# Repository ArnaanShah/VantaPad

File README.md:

# VantaPad 👽

A Hackpad made as a part of [Hackclub's Blueprint](https://blueprint.hackclub.com/home) program. VantaPad is a sleek black macropad I will use for controlling simple functions on my computer that I currently do by hand. It is one of my first hardware projects and I built it so I could learn many valuable skills such as schematic design, PCB design, Firmware programming, and more.

## How to use
**Brief intro on how to get up and running with VantaPad**

1. Order all the parts based off the BOM
2. Solder your electrical components onto your PCB based on the models and schematics
3. Assemble your case using the hardware provided
4. Plug your microcontroller into your computer and flash your firmware
5. You're done! Read the rest of this doc to understand what it can do.

## Features 
**What I included on my build.**

- Black Case - A case in the shape of a hexagon with the logo embossed near the bottom.
- 6 Keys in 3x2 layout - Top row is used for resetting screen, taking screenshots, and play/pause. Bottom row has macros for reopening tabs, auto clicking, and cycling layers.  
- 3 RGB LEDs - Lights up a constant looping effect that fades in and out through the case. 
- Rotary Encoder - Layer 1 is Volume, Layer 2 is Tab Scrolling, Layer 3 is undo/redo
- 128x32 OLED Display - Shows important info like what layer you're on and auto clicker status. Also, shows idle animations and reactions when you press a key.
  
## PCB 
**The design around my PCB. This Includes the schematic I made, the PCB, and more.** 

I designed my PCB in KiCad 9.0! It was fun to use this app because it was pretty beginner friendly and intuitive. It also had some extra built in features so I didn't have to download another app.

Schematic: 

PCB:

3d VIEW:

I used KiCad's built-in Image Converter to make a footprint of my logo:

## CAD
**The CAD model I made.**

I modeled this project in Fusion 360 because I've used it before. My plan is that I can assemble the whole thing with 6 screws. 4 on the actual case and 2 connecting the PCB and PCB plate to the case. I added a 10 degree tilt to make it easier to see. There are 3 separate 3d printed parts; the top, the plate, and the bottom. The top has the VantaPad logo on it because it looks lit. 😎

Pictures 📸:

## Firmware 
**Insight into the Firmware**

I wrote all the firmware in QMK. I spent a long time fixing problems when writing the code. These problems were things like the firmware not compiling, not knowing how to use all my extra features, and more. The QMK docs can be confusing but I found many resources online to help me. 

- The 6 keys are mapped as shown but can be easily changed
```
║ Screen Reset ║ Screenshot   ║ Play/Pause  ║

║ Reopen Tab   ║ Auto Clicker ║ Layer Cycle ║
```
```// ---------- Keymaps ----------
const uint16_t PROGMEM keymaps[][MATRIX_ROWS][MATRIX_COLS] = {
    [_BASE] = LAYOUT(
        RESET_SCREEN, SCREENSHOT, KC_MPLY, KC_MUTE, // Top row + Encoder Button
        REOPEN_TAB, AUTO_CLICKER, KC_CYCLE_LAYERS
    ),
};
```
- The rotary encoder controls volume on the first layer, scrolls through browser tabs on the second layer, and undos/redos on the third layer.
  - When you press down on the encoder it always mutes the volume
```
const uint16_t PROGMEM encoder_map[][1][2] = {
    [_BASE]   = { ENCODER_CCW_CW(KC_VOLD, KC_VOLU) },
    [_LAYER1] = { ENCODER_CCW_CW(LCTL(KC_PGUP), LCTL(KC_PGDN)) },
    [_LAYER2] = { ENCODER_CCW_CW(LCTL(KC_Z), LCTL(KC_Y)) },
};
```
- The OLED has 2 animations. Animation 1 is the constant looping animation where my alien is "breathing" with occasional blinks. Animation 2 starts when any key is pressed and it basically makes the alien look surprised and have a lightning bolt above his head. 

- The OLED also has some info on the left of the animation. This includes what layer it is currently using, whether the auto clicker is on, the label "Vantapad", and also my name. 
```
oled_set_cursor(0, 0);
    oled_write_P(PSTR("Arnaan Shah"), false);

    oled_set_cursor(0, 1);
    oled_write_P(PSTR("Vantapad"), false);

    oled_set_cursor(0, 2);
    switch (get_highest_layer(layer_state)) {
        case _BASE:   oled_write_P(PSTR("Layer 1"), false); break;
        case _LAYER1: oled_write_P(PSTR("Layer 2"), false); break;
        case _LAYER2: oled_write_P(PSTR("Layer 3"), false); break;
    }

    oled_set_cursor(0, 3);
    if (auto_clicker_active) {
        oled_write_P(PSTR("AutoClick:ON "), false);
    } else {
        oled_write_P(PSTR("AutoClick:OFF"), false);
    }
```

- The RGB LEDS are set to display red and cycle a constant breathing animation
```
void keyboard_post_init_user(void) {
    rgblight_enable_noeeprom();
    rgblight_sethsv_noeeprom(0, 255, 100);
    rgblight_mode_noeeprom(RGBLIGHT_MODE_BREATHING + 1); 
}
```
## BOM
**What to buy to build this macropad. Does not include all the tools required to build it.**

| Name | Amount | Link |
|---|---|---|
| Cherry MX Switches | 6 | [Adafruit](https://www.adafruit.com/product/4952)|
| DSA Keycaps | 6 | [Adafruit](https://www.adafruit.com/product/4997?srsltid=AfmBOopDyFMg5RxxF-Evr6nBGQDyHVTH-dyfbuGdqPaHn7PWQv5c8-_Q) |
| M3 16mm SHCS Bolts | 5 | [Accu Components](https://accu-components.com/us/metric-cap-head-screws/3822-SSCF-M3-16-A2?srsltid=AfmBOopF9mJr7xpYuq4pjtawdEtUoNOIrShH98uHL0dEVVrOUcjwKY9b) |
| M3 12mm SHCS Bolt | 1 | [Accu Components](https://accu-components.com/us/metric-cap-head-screws/3820-SSCF-M3-12-A2) |
| M3 Hex Nuts | 6 | [Accu Components](https://accu-components.com/us/hexagon-nuts/7888-HPN-M3-A2) |
| In4148 DO-35 Diodes | 7 | [Adafruit](https://www.adafruit.com/product/1641?srsltid=AfmBOoragpyopdxH587co8w9Kl0W3cZMjn9bZIbP4UEYHfyiLFoC3nJv) |
| WS2812B RGB LEDS | 3 | [Adafruit](https://www.adafruit.com/product/4684?srsltid=AfmBOop-1QOhPkmYg3AzDhOUYgR5UXpQo03Vo2tT4txB9Lo8MBpf2Z1e) |
| 0.91" OLED Display | 1 | [Aliexpress](https://www.aliexpress.us/item/3256807215355950.html?src=google&pdp_npi=4%40dis%21USD%211.75%210.87%21%21%21%21%21%40%2112000040595474261%21ppc%21%21%21&src=google&albch=shopping&acnt=708-803-3821&isdl=y&slnk=&plac=&mtctp=&albbt=Google_7_shopping&aff_platform=google&aff_short_key=UneMJZVf&gclsrc=aw.ds&albagn=888888&ds_e_adid=&ds_e_matchtype=&ds_e_device=c&ds_e_network=x&ds_e_product_group_id=&ds_e_product_id=en3256807215355950&ds_e_product_merchant_id=5377576114&ds_e_product_country=US&ds_e_product_language=en&ds_e_product_channel=online&ds_e_product_store_id=&ds_url_v=2&albcp=19558607238&albag=&isSmbAutoCall=false&needSmbHouyi=false&gad_source=1&gad_campaignid=19566915268&gclid=Cj0KCQiAk6rNBhCxARIsAN5mQLsg54LCOzQhSObuPu2m54rcTcgSLZ9bMY2AuwFurhrSghMghQPbqsoaAguWEALw_wcB&gatewayAdapt=glo2usa)|
| EC11 Encoder | 1 | [Adafruit](https://www.adafruit.com/product/377)|
| Seeed Studio XIAO RP2040 | 1 | [Seeed Studio](https://www.seeedstudio.com/XIAO-RP2040-v1-0-p-5026.html) |
| 3d Printed Case | 1 | N/A |

## Extras 🪄
**Miscellaneous related things**

I made the logo design all in Figma and it's based off the "Space Alien" inside Halloween Stickers. 

It's honestly one of my favorite parts of the project because of how cute he is 😅

_

Here are some photos of my brainstorming process. It includes some (really) rough sketches in my notebook and also online. 

_I always start with doing things in my notebook and then move forward from there. It helps me get a very basic idea of what im going to do and how to accomplish it._

_I made this image afterwards just to get a better understanding of how I wanted it to look._

Changes I would still consider making down the line include: 
1. More Information displayed on the OLED - WPM, Time, Date, Volume
2. Adding more animations to the OLED - Spinning alien based on knob, startup screen
3. Making the RGB react - Flash on key press, blink when auto-clicker's active
4. Displaying the PCB through the case somehow

Some resources I used:
- [Joe Scotto's Youtube Channel](https://www.youtube.com/@joe_scotto) (LIFESAVER 🙏)
- [QMK Docs](https://docs.qmk.fm)
- [r/MechanicalKeyboards subreddit](https://www.reddit.com/r/MechanicalKeyboards/) 

# Thanks for reading! If you have any feedback, comments, or questions I would love to hear them and you can always reach out to me!

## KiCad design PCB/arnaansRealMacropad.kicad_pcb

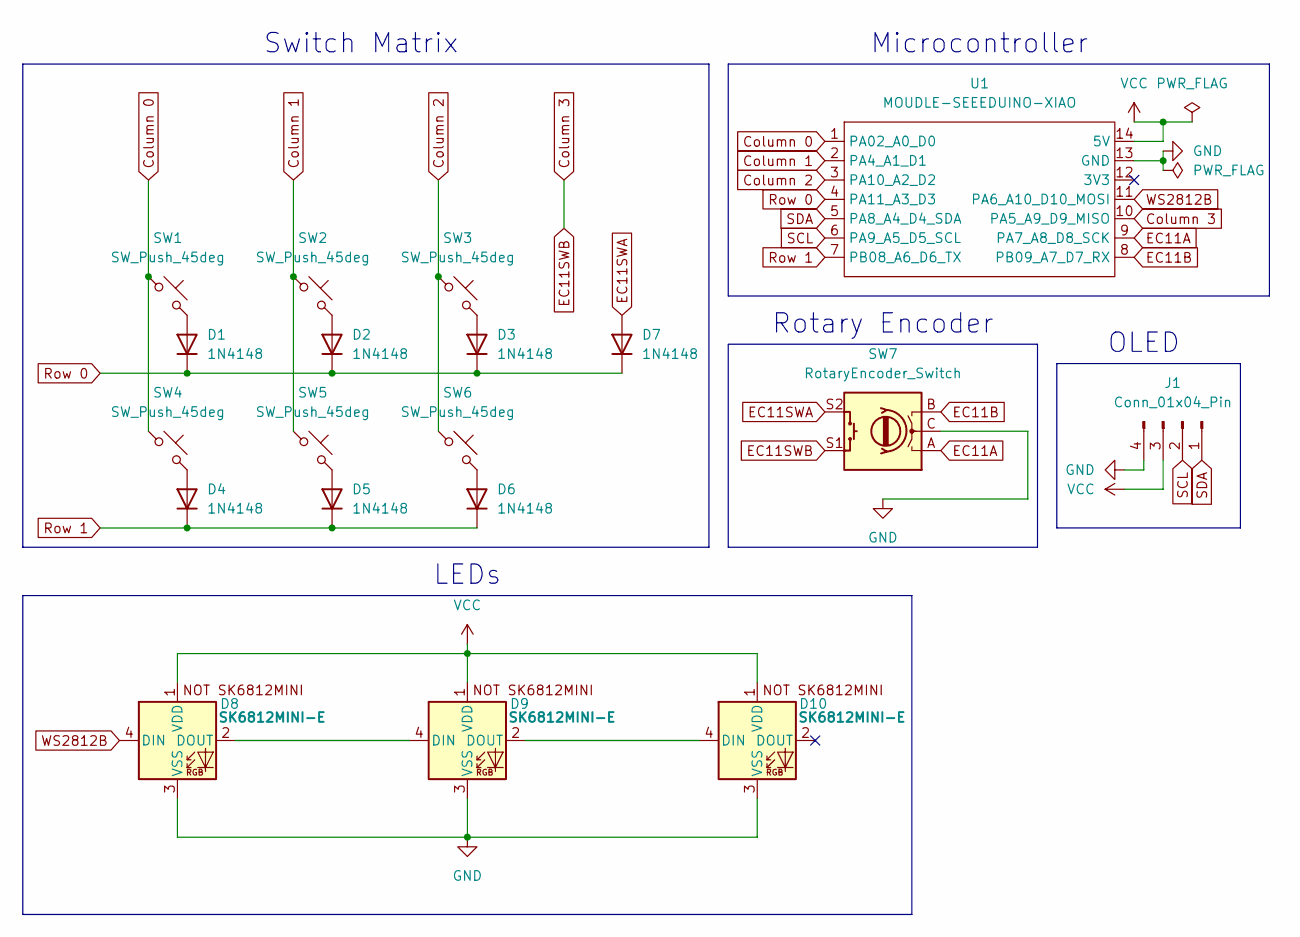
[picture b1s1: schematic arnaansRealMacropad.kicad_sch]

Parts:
D1, D2, D3, D4, D5, D6, D7: 1N4148; D_DO-35_SOD27_P7.62mm_Horizontal
D8, D9, D10: SK6812MINI-E; SK6812MINI-E_fixed
J1: Conn_01x04_Pin; PinHeader_1x04_P2.54mm_Vertical
SW1, SW2, SW3, SW4, SW5, SW6: SW_Push_45deg; SW_Cherry_MX_1.00u_PCB
SW7: RotaryEncoder_Switch; RotaryEncoder_Alps_EC11E-Switch_Vertical_H20mm
U1: MOUDLE-SEEEDUINO-XIAO; XIAO-Generic-Hybrid-14P-2.54-21X17.8MM

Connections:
Column 0: SW1.1, SW4.1, U1.1 (PA02_A0_D0)
Column 1: SW2.1, SW5.1, U1.2 (PA4_A1_D1)
Column 2: SW3.1, SW6.1, U1.3 (PA10_A2_D2)
Column 3: SW7.S1, U1.10 (PA5_A9_D9_MISO)
EC11A: SW7.A, U1.9 (PA7_A8_D8_SCK)
EC11B: SW7.B, U1.8 (PB09_A7_D7_RX)
EC11SWA: D7.2 (A), SW7.S2
GND: D8.3 (VSS), D9.3 (VSS), D10.3 (VSS), J1.4, SW7.C, U1.13 (GND)
unnamed: D1.2 (A), SW1.2
unnamed: D2.2 (A), SW2.2
unnamed: D3.2 (A), SW3.2
unnamed: D4.2 (A), SW4.2
unnamed: D5.2 (A), SW5.2
unnamed: D6.2 (A), SW6.2
unnamed: D8.2 (DOUT), D9.4 (DIN)
unnamed: D9.2 (DOUT), D10.4 (DIN)
Row 0: D1.1 (K), D2.1 (K), D3.1 (K), D7.1 (K), U1.4 (PA11_A3_D3)
Row 1: D4.1 (K), D5.1 (K), D6.1 (K), U1.7 (PB08_A6_D6_TX)
SCL: J1.2, U1.6 (PA9_A5_D5_SCL)
SDA: J1.1, U1.5 (PA8_A4_D4_SDA)
VCC: D8.1 (VDD), D9.1 (VDD), D10.1 (VDD), J1.3, U1.14 (5V)
WS2812B: D8.4 (DIN), U1.11 (PA6_A10_D10_MOSI)

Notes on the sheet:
Rotary Encoder
OLED
Microcontroller
Switch Matrix
LEDs

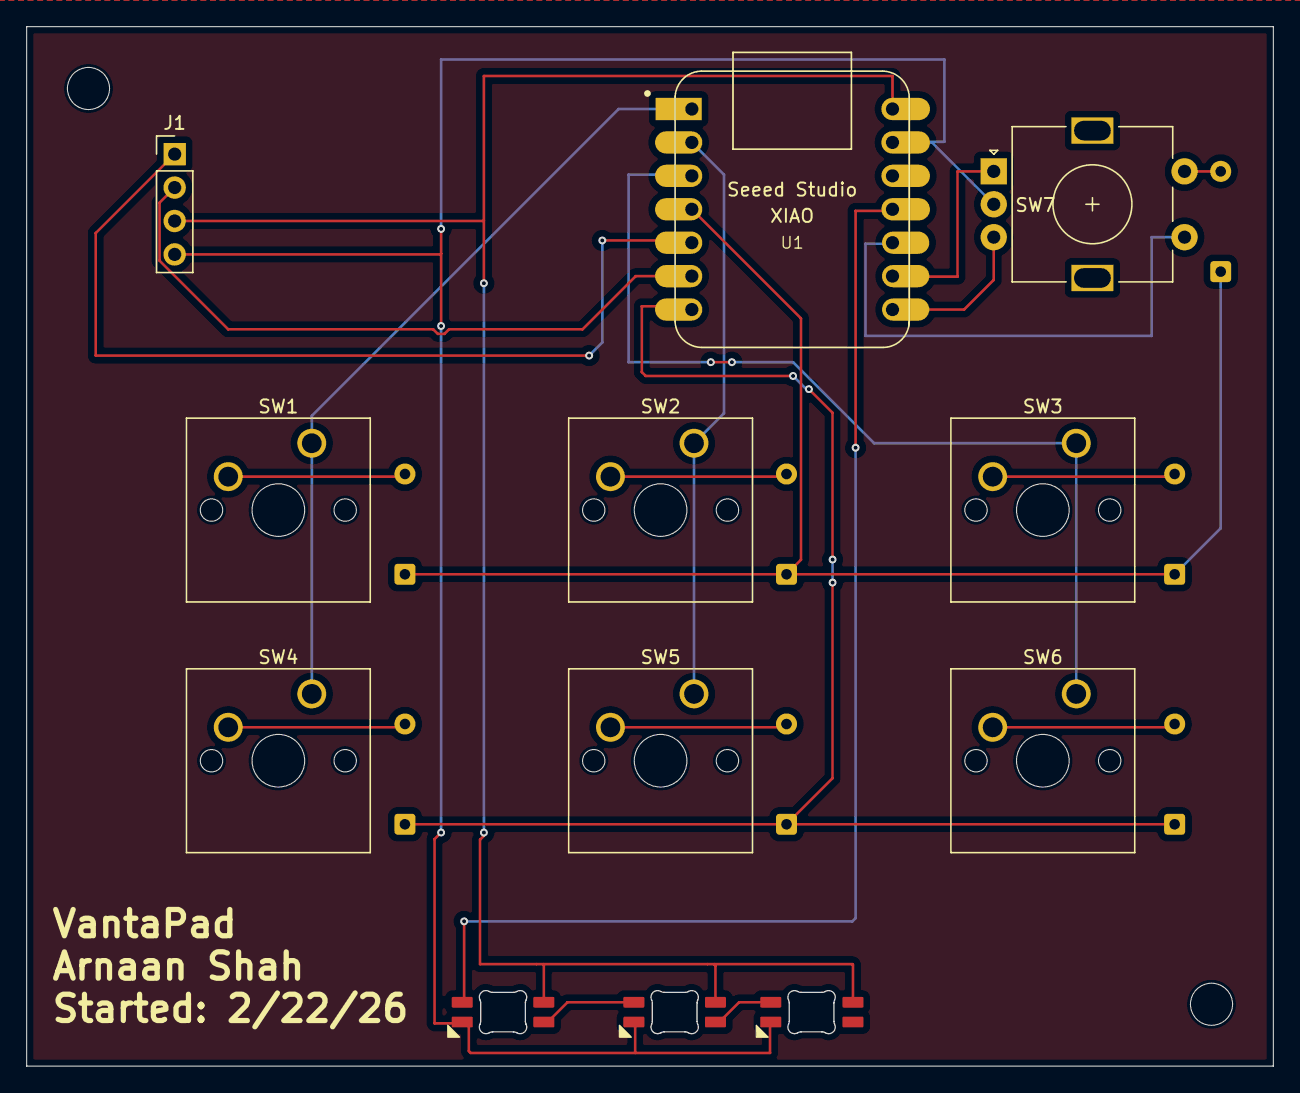
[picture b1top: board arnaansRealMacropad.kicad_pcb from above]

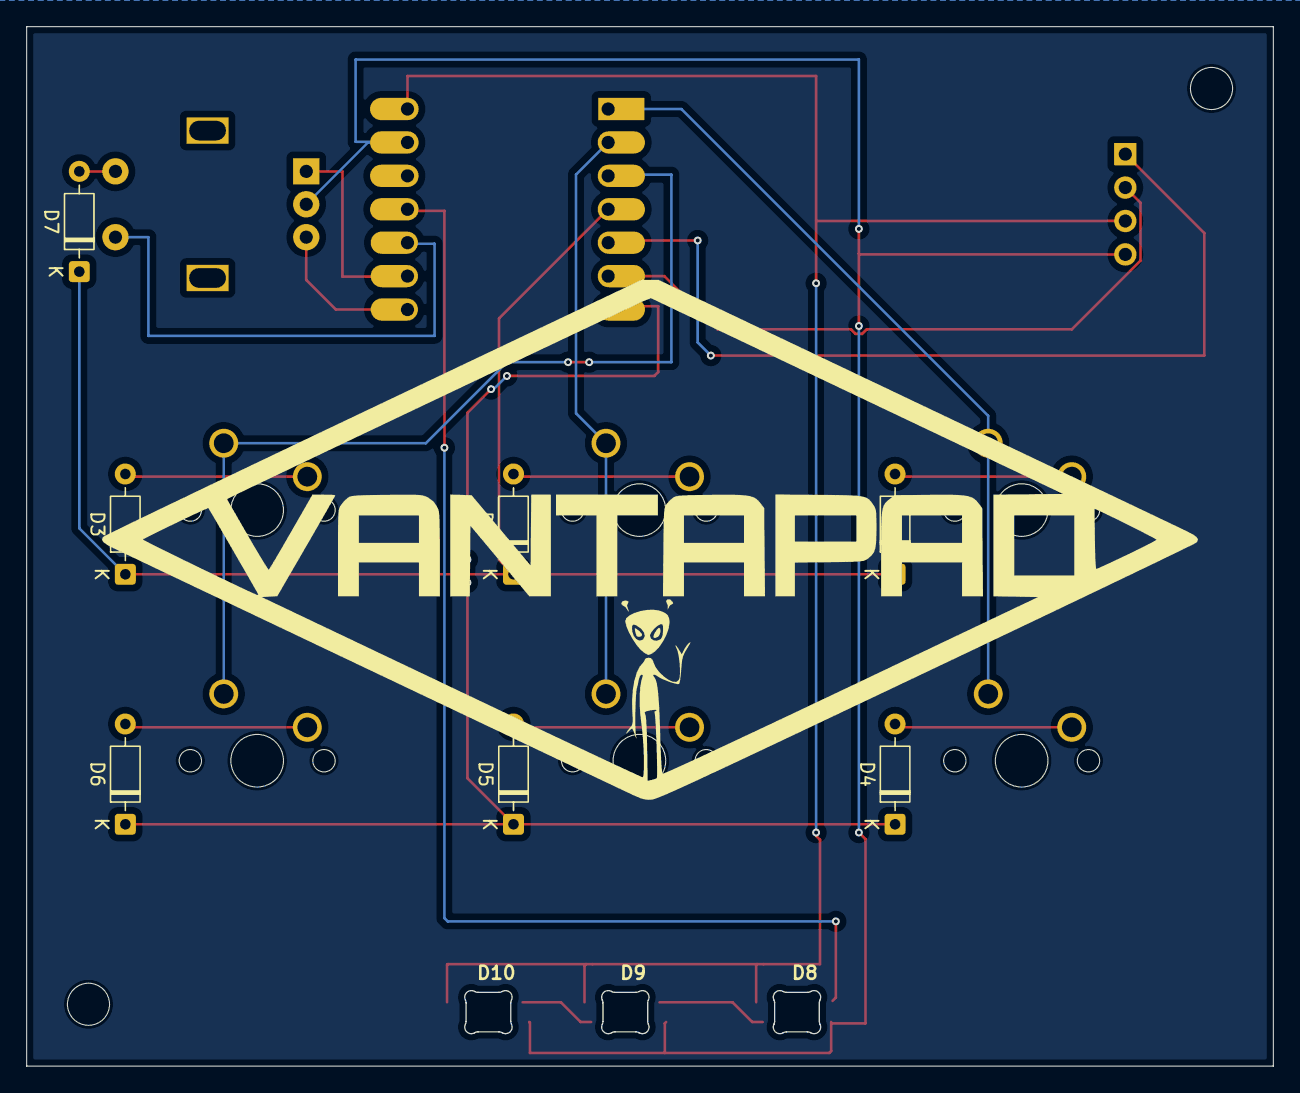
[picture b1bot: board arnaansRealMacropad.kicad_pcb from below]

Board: 2 copper layers, 94.8 x 79.0 mm, 19 parts (10 on the bottom side), 22 nets.

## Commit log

2026-03-06 Added the required files
2026-03-06 Refactor README.md for better structure and clarity
    Updated the README to improve formatting and content clarity.
2026-03-06 Enhance README with images and hyperlinks
    Updated README.md to include images and links.
2026-03-07 Add BOM.csv with components and links
2026-03-07 Enhance README with design process and images
    Added brainstorming process photos and design insights.
2026-03-07 Refine image layout and remove unnecessary breaks
    Removed extra line breaks and added a smaller image for better layout.
2026-03-07 Add additional details about logo design process
2026-03-07 Update README with brainstorming photos and comments
    Added additional images and personal reflections on the project.
2026-03-08 Fixed LED footprint
2026-03-08 Fix typo in 'Features' section header
2026-03-30 Fixed walls being too thin in CAD file
2026-04-05 Fixing and debugging Firmware
2026-04-07 Finishing Firmware and debugging OLED
2026-04-07 Addded Journal to show build
2026-04-07 Updated Readme and added photos/videos
